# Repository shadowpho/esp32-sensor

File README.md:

# esp32-sensor
ESP32-S2 host, HDC2080 temp/humidity sensor with optional display.

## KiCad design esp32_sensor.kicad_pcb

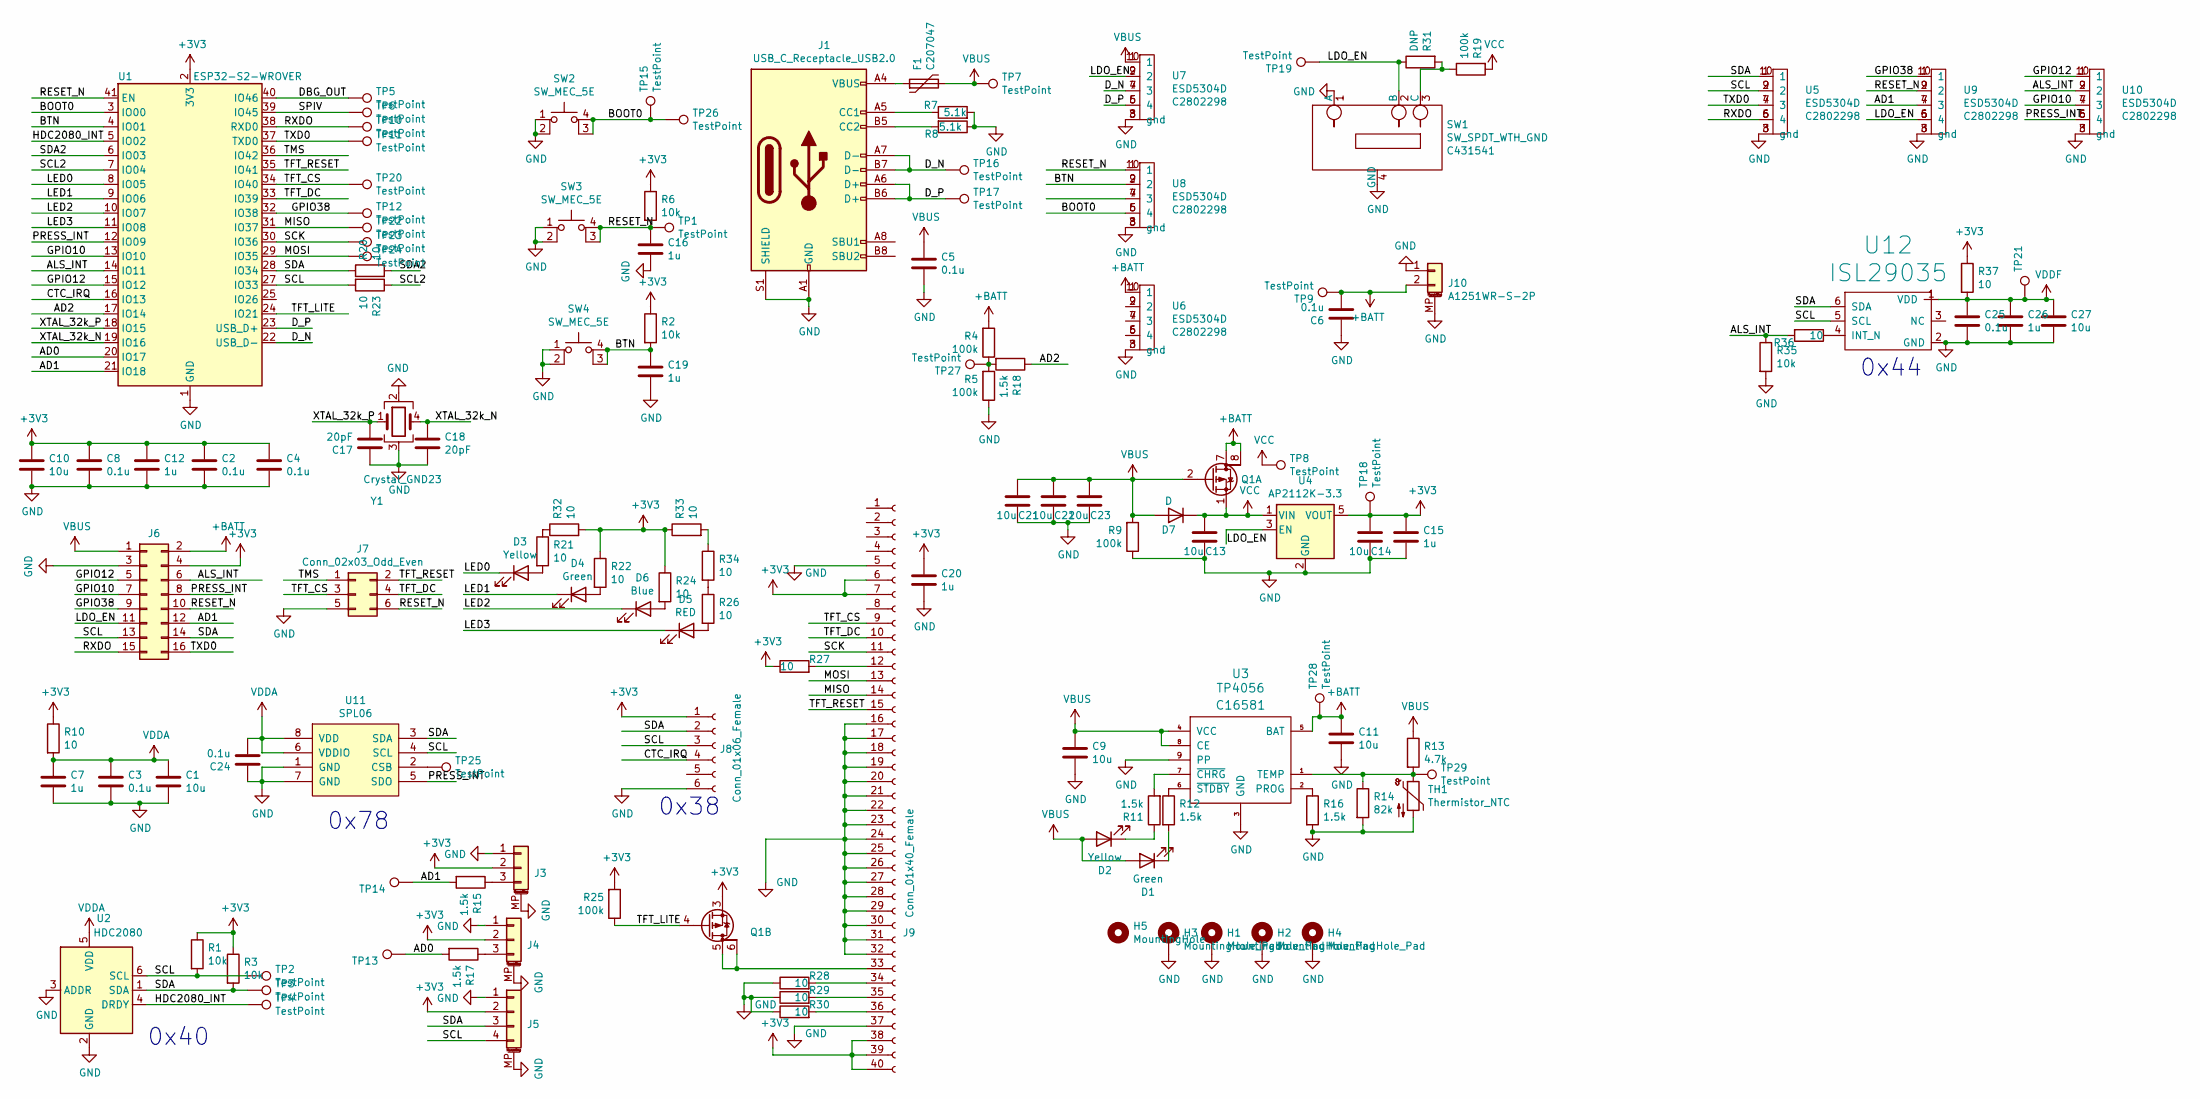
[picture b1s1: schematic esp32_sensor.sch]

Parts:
C1, C9, C10, C11, C13, C14, C21, C22, C23, C27: 10u; C_0603_1608Metric
C2, C3, C4, C5, C6, C8, C24, C25: 0.1u; C_0402_1005Metric
C7, C12, C15, C16, C19, C20, C26: 1u; C_0402_1005Metric
C17, C18: 20pF; C_0402_1005Metric; LCSC C1554
D1, D4: Green; LED_0805_2012Metric; LCSC C2297
D2, D3: Yellow; LED_0805_2012Metric; LCSC C2296
D5: RED; LED_0805_2012Metric; LCSC C84256
D6: Blue; LED_0603_1608Metric; LCSC C72041
D7: D; D_SMA_DO-214AC; LCSC C8678
F1: C207047; L_1210_3225Metric; lcsc C135353
H1, H2, H3, H4: MountingHole_Pad; MountingHole_2.7mm_M2.5
H5: MountingHole; MountingHole_2.5mm
J1: USB_C_Receptacle_USB2.0; USB_C_Receptacle_Palconn_UTC16-G; LCSC C381475
J3, J4: Conn_01x03_MountingPin; Molex_CLIK-Mate_502443-0370_1x03-1MP_P2.00mm_Vertical; lcsc C225234
J5: Conn_01x04_MountingPin; Molex_CLIK-Mate_502443-0470_1x04-1MP_P2.00mm_Vertical; lcsc C225235
J6: DNP; PinHeader_2x08_P2.54mm_Vertical
J7: Conn_02x03_Odd_Even; Tag-Connect_TC2030-IDC-NL_2x03_P1.27mm_Vertical
J8: Conn_01x06_Female; Hirose_FH12-6S-0.5SH_1x06-1MP_P0.50mm_Horizontal; LCSC C262262
J9: Conn_01x40_Female; Hirose_FH12-40S-0.5SH_1x40-1MP_P0.50mm_Horizontal_flipped; LCSC C11097
J10: A1251WR-S-2P; Molex_PicoBlade_53261-0271_1x02-1MP_P1.25mm_Horizontal; LCSC C225111
Q1: Q_DUAL_PMOS_S1G1S2G2D2D2D1D1; SO-8_3.9x4.9mm_P1.27mm; lcsc C20897
R1, R2, R3, R6, R35: 10k; R_0402_1005Metric
R4, R5, R9, R19, R25: 100k; R_0402_1005Metric
R7, R8: 5.1k; R_0402_1005Metric
R10, R20, R21, R22, R23, R24, R26, R27, R28, R29, R30, R32, R33, R34, R36, R37: 10; R_0402_1005Metric
R11, R12, R15, R16, R17, R18: 1.5k; R_0402_1005Metric
R13: 4.7k; R_0402_1005Metric
R14: 82k; R_0603_1608Metric; LCSC C23254
R31: DNP; R_0402_1005Metric
SW1: SW_SPDT_WTH_GND; MSK12C02; LCSC C431541
SW2, SW3, SW4: SW_MEC_5E; SW_SPST_B3S-1000; LCSC C127509
TH1: Thermistor_NTC; R_0805_2012Metric; LCSC C95968
TP1, TP2, TP3, TP4, TP5, TP6, TP7, TP8, TP9, TP10, TP11, TP12, TP13, TP14, TP15, TP16, TP17, TP18, TP19, TP20, TP21, TP22, TP23, TP24, TP25, TP26, TP27, TP28, TP29: TestPoint; TestPoint_Pad_D2.0mm
U1: ESP32-S2-WROVER; LCSC C701333
U2: HDC2080; Texas_PWSON-N6; LCSC C266121
U3: TP4056; TP4056_SOP-8-PP
U4: AP2112K-3.3; SOT-23-5; lcsc C51118
U5, U6, U7, U8, U9, U10: ESD5304D; Diodes_UDFN-10_1.0x2.5mm_P0.5mm; LCSC C2802298
U11: SPL06; Bosch_LGA-8_2x2.5mm_P0.65mm_ClockwisePinNumbering
U12: ISL29035; ISL29035-DFN-6-1.5x1.6mm_Pitch0.5mm_HC
Y1: Crystal_GND23; Crystal_SMD_SeikoEpson_MC306-4Pin_8.0x3.2mm; LCSC C145166

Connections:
+3V3: C2.1, C4.1, C8.1, C10.1, C12.1, C14.1, C15.1, C20.1, J3.2, J4.2, J5.2, J6.4, J8.1, J9.6, J9.7, J9.38, J9.39, J9.40, Q1.3 (S), R1.1, R2.1, R3.1, R6.1, R10.1, R22.1, R24.1, R25.2, R27.1, R32.2, R33.1, R37.1, TP18.1, U1.2 (3V3), U4.5 (VOUT)
+BATT: C6.2, C11.1, J6.2, J10.2, Q1.7 (D), Q1.8 (G), R4.2, TP9.1, TP28.1, U3.5 (BAT), U6.1, U6.10 (1)
/AD0: R17.2, TP13.1, U1.20 (IO17)
/AD1: J6.12, R15.2, TP14.1, U1.21 (IO18), U9.4 (3), U9.7 (3)
/AD2: R18.1, U1.17 (IO14)
/ALS_INT: J6.6, R35.1, R36.2, U1.14 (IO11), U10.2, U10.9 (2)
/BOOT0: SW2.3 (K), SW2.4 (A), TP15.1, TP26.1, U1.3 (IO00), U8.5 (4), U8.6 (4)
/BTN: C19.1, R2.2, SW4.3 (K), SW4.4 (A), U1.4 (IO01), U8.2, U8.9 (2)
/CTC_IRQ: J8.4, U1.16 (IO13)
/DBG_OUT: TP5.1, U1.40 (IO46)
/D_N: J1.A7 (D-), J1.B7 (D-), TP16.1, U1.22 (USB_D-), U7.4 (3), U7.7 (3)
/D_P: J1.A6 (D+), J1.B6 (D+), TP17.1, U1.23 (USB_D+), U7.5 (4), U7.6 (4)
/GPIO10: J6.7, U1.13 (IO10), U10.4 (3), U10.7 (3)
/GPIO12: J6.5, U1.15 (IO12), U10.1, U10.10 (1)
/GPIO38: J6.9, TP12.1, U1.32 (IO38), U9.1, U9.10 (1)
/HDC2080_INT: TP4.1, U1.5 (IO02), U2.4 (DRDY)
/LDO_EN: J6.11, R31.1, SW1.2 (B), TP19.1, U4.3 (EN), U7.2, U7.9 (2), U9.5 (4), U9.6 (4)
/LED0: D3.1 (K), U1.8 (IO05)
/LED1: D4.1 (K), U1.9 (IO06)
/LED2: D6.1 (K), U1.10 (IO07)
/LED3: D5.1 (K), U1.11 (IO08)
/MISO: J9.14, TP22.1, U1.31 (IO37)
/MOSI: J9.13, TP24.1, U1.29 (IO35)
/PRESS_INT: J6.8, U1.12 (IO09), U10.5 (4), U10.6 (4), U11.5 (SDO)
/RESET_N: C16.1, J6.10, J7.6, R6.2, SW3.3 (K), SW3.4 (A), TP1.1, U1.41 (EN), U8.1, U8.10 (1), U9.2, U9.9 (2)
/RXDO: J6.15, TP10.1, U1.38 (RXD0), U5.5 (4), U5.6 (4)
/SCK: J9.11, TP23.1, U1.30 (IO36)
/SCL: J5.4, J6.13, J8.3, R1.2, R23.2, TP2.1, U1.27 (IO33), U2.6 (SCL), U5.2, U5.9 (2), U11.4 (SCL), U12.5 (SCL)
/SCL2: R23.1, U1.7 (IO04)
/SDA: J5.3, J6.14, J8.2, R3.2, R20.1, TP3.1, U1.28 (IO34), U2.1 (SDA), U5.1, U5.10 (1), U11.3 (SDA), U12.6 (SDA)
/SDA2: R20.2, U1.6 (IO03)
/SPIV: TP6.1, U1.39 (IO45)
/TFT_CS: J7.3, J9.9, TP20.1, U1.34 (IO40)
/TFT_DC: J7.4, J9.10, U1.33 (IO39)
/TFT_LITE: Q1.4 (G), R25.1, U1.24 (IO21)
/TFT_RESET: J7.2, J9.15, U1.35 (IO41)
/TMS: J7.1, U1.36 (IO42)
/TXD0: J6.16, TP11.1, U1.37 (TXD0), U5.4 (3), U5.7 (3)
/XTAL_32k_N: C18.1, U1.19 (IO16), Y1.4
/XTAL_32k_P: C17.2, U1.18 (IO15), Y1.1
GND: C1.2, C2.2, C3.2, C4.2, C5.2, C6.1, C7.2, C8.2, C9.2, C10.2, C11.2, C12.2, C13.2, C14.2, C15.2, C16.2, C17.1, C18.2, C19.2, C20.2, C21.2, C22.2, C23.2, C24.1, C25.2, C26.2, C27.2, H1.1, H2.1, H3.1, H4.1, J1.A1 (GND), J1.A12 (GND), J1.B1 (GND), J1.B12 (GND), J1.S1 (SHIELD), J3.1, J3.MP (MountPin), J4.1, J4.MP (MountPin), J5.1, J5.MP (MountPin), J6.3, J7.5, J8.6, J9.5, J9.16, J9.17, J9.18, J9.19, J9.20, J9.21, J9.22, J9.23, J9.24, J9.25, J9.26, J9.27, J9.28, J9.29, J9.30, J9.31, J9.32, J9.37, J10.1, J10.MP (MountPin), R5.1, R7.2, R8.1, R9.1, R14.2, R16.2, R28.1, R29.1, R30.1, R35.2, SW1.1 (A), SW1.4 (GND), SW2.1, SW2.2, SW3.1, SW3.2, SW4.1, SW4.2, TH1.2, U1.1 (GND), U1.26 (GND), U1.42 (GND), U1.43 (GND), U2.2 (GND), U2.3 (ADDR), U3.3 (GND), U3.9 (PP), U4.2 (GND), U5.3 (gnd), U5.8 (gnd), U6.3 (gnd), U6.8 (gnd), U7.3 (gnd), U7.8 (gnd), U8.3 (gnd), U8.8 (gnd), U9.3 (gnd), U9.8 (gnd), U10.3 (gnd), U10.8 (gnd), U11.1 (GND), U11.7 (GND), U12.2 (GND), Y1.2, Y1.3
unnamed: D1.1 (K), R12.2
unnamed: D2.1 (K), R11.1
unnamed: D3.2 (A), R21.2
unnamed: D4.2 (A), R22.2
unnamed: D5.2 (A), R26.2
unnamed: D6.2 (A), R24.2
unnamed: F1.1, J1.A4 (VBUS), J1.A9 (VBUS), J1.B4 (VBUS), J1.B9 (VBUS)
unnamed: J1.A5 (CC1), R7.1
unnamed: J1.B5 (CC2), R8.2
unnamed: J3.3, R15.1
unnamed: J4.3, R17.1
unnamed: J9.12, R27.2
unnamed: J9.33, Q1.5 (D), Q1.6 (G)
unnamed: J9.34, R28.2
unnamed: J9.35, R29.2
unnamed: J9.36, R30.2
unnamed: R11.2, U3.7 (~CHRG)
unnamed: R12.1, U3.6 (~STDBY)
unnamed: R13.2, R14.1, TH1.1, TP29.1, U3.1 (TEMP)
unnamed: R16.1, U3.2 (PROG)
unnamed: R4.1, R5.2, R18.2, TP27.1
unnamed: R19.1, R31.2, SW1.3 (C)
unnamed: R21.1, R32.1
unnamed: R26.1, R34.2
unnamed: R33.2, R34.1
unnamed: R36.1, U12.4 (INT_N)
unnamed: TP25.1, U11.2 (CSB)
unnamed: U6.2, U6.9 (2)
unnamed: U6.4 (3), U6.7 (3)
unnamed: U6.5 (4), U6.6 (4)
unnamed: U8.4 (3), U8.7 (3)
VBUS: C5.1, C9.1, C21.1, C22.1, C23.1, D1.2 (A), D2.2 (A), D7.2 (A), F1.2, J6.1, Q1.2 (G), R9.2, R13.1, TP7.1, U3.4 (VCC), U3.8 (CE), U7.1, U7.10 (1)
VCC: C13.1, D7.1 (K), Q1.1 (S), R19.2, TP8.1, U4.1 (VIN)
VDDA: C1.1, C3.1, C7.1, C24.2, R10.2, U2.5 (VDD), U11.6 (VDDIO), U11.8 (VDD)
VDDF: C25.1, C26.1, C27.1, R37.2, TP21.1, U12.1 (VDD)

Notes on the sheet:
0x40
0x38
0x78
0x44

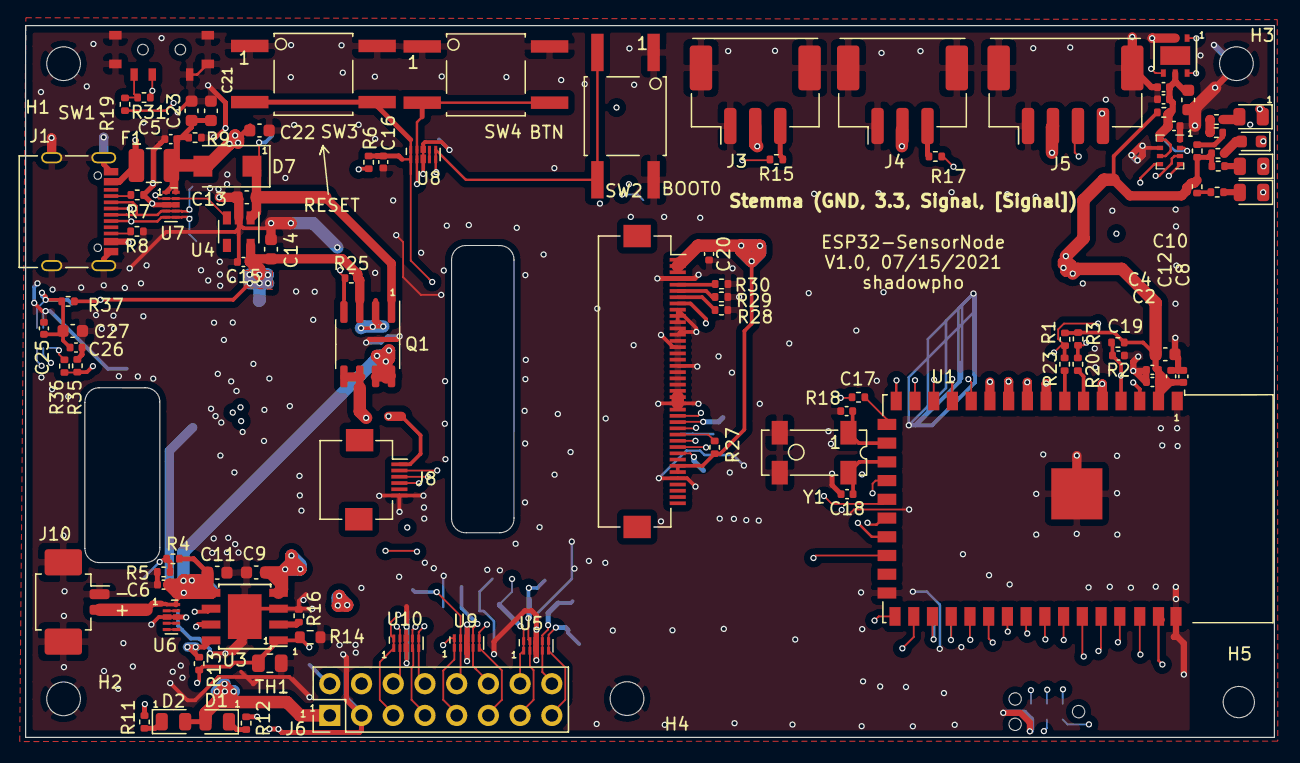
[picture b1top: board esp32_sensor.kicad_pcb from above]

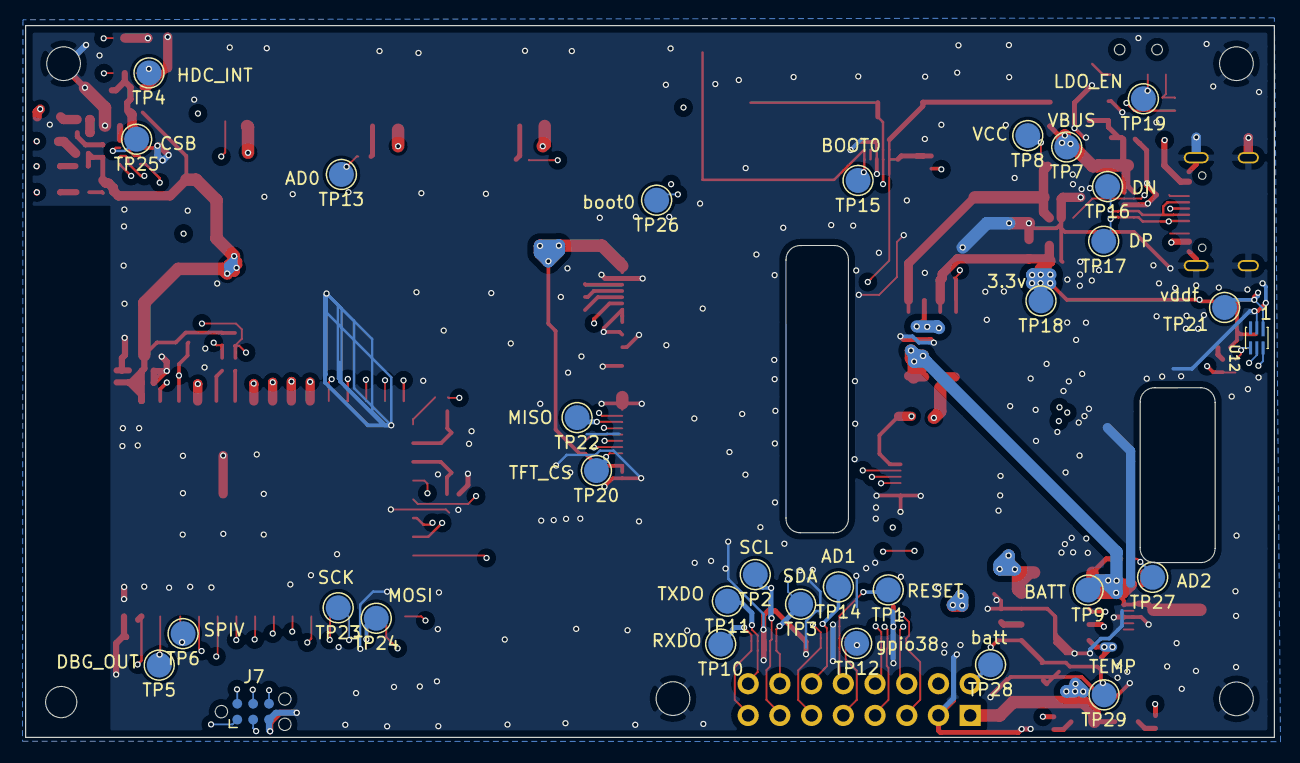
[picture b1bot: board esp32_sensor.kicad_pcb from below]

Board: 4 copper layers, 100.0 x 57.0 mm, 134 parts (31 on the bottom side), 76 nets.

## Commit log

2021-07-18 V1 sent to jlcpcb
